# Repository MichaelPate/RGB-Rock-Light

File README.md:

# RGB Rock Light
 RGB LED decoration for a big crystal. This code is designed for an ATTiny85. Its meant to be powered over USB and just sits around as a decoration.
 This is currently v2 of the design. It uses the built in EEPROM library, the Adafruit NeoPixel library, and the ATTiny board manager URL from:
 https://raw.githubusercontent.com/damellis/attiny/ide-1.6.x-boards-manager/package_damellis_attiny_index.json

To program the board more easily, I designed a programmer shield for an Arduino Uno that lets me use a programming cable on JST PH headers.
See the link below to that repo. https://github.com/MichaelPate/Arduino-ISP-PROgrammer-Shield/tree/main

I will eventually get around to designing an enclosure for this. When that happens, ill put it on thingiverse and add the link here!
https://www.thingiverse.com/thing:7125638

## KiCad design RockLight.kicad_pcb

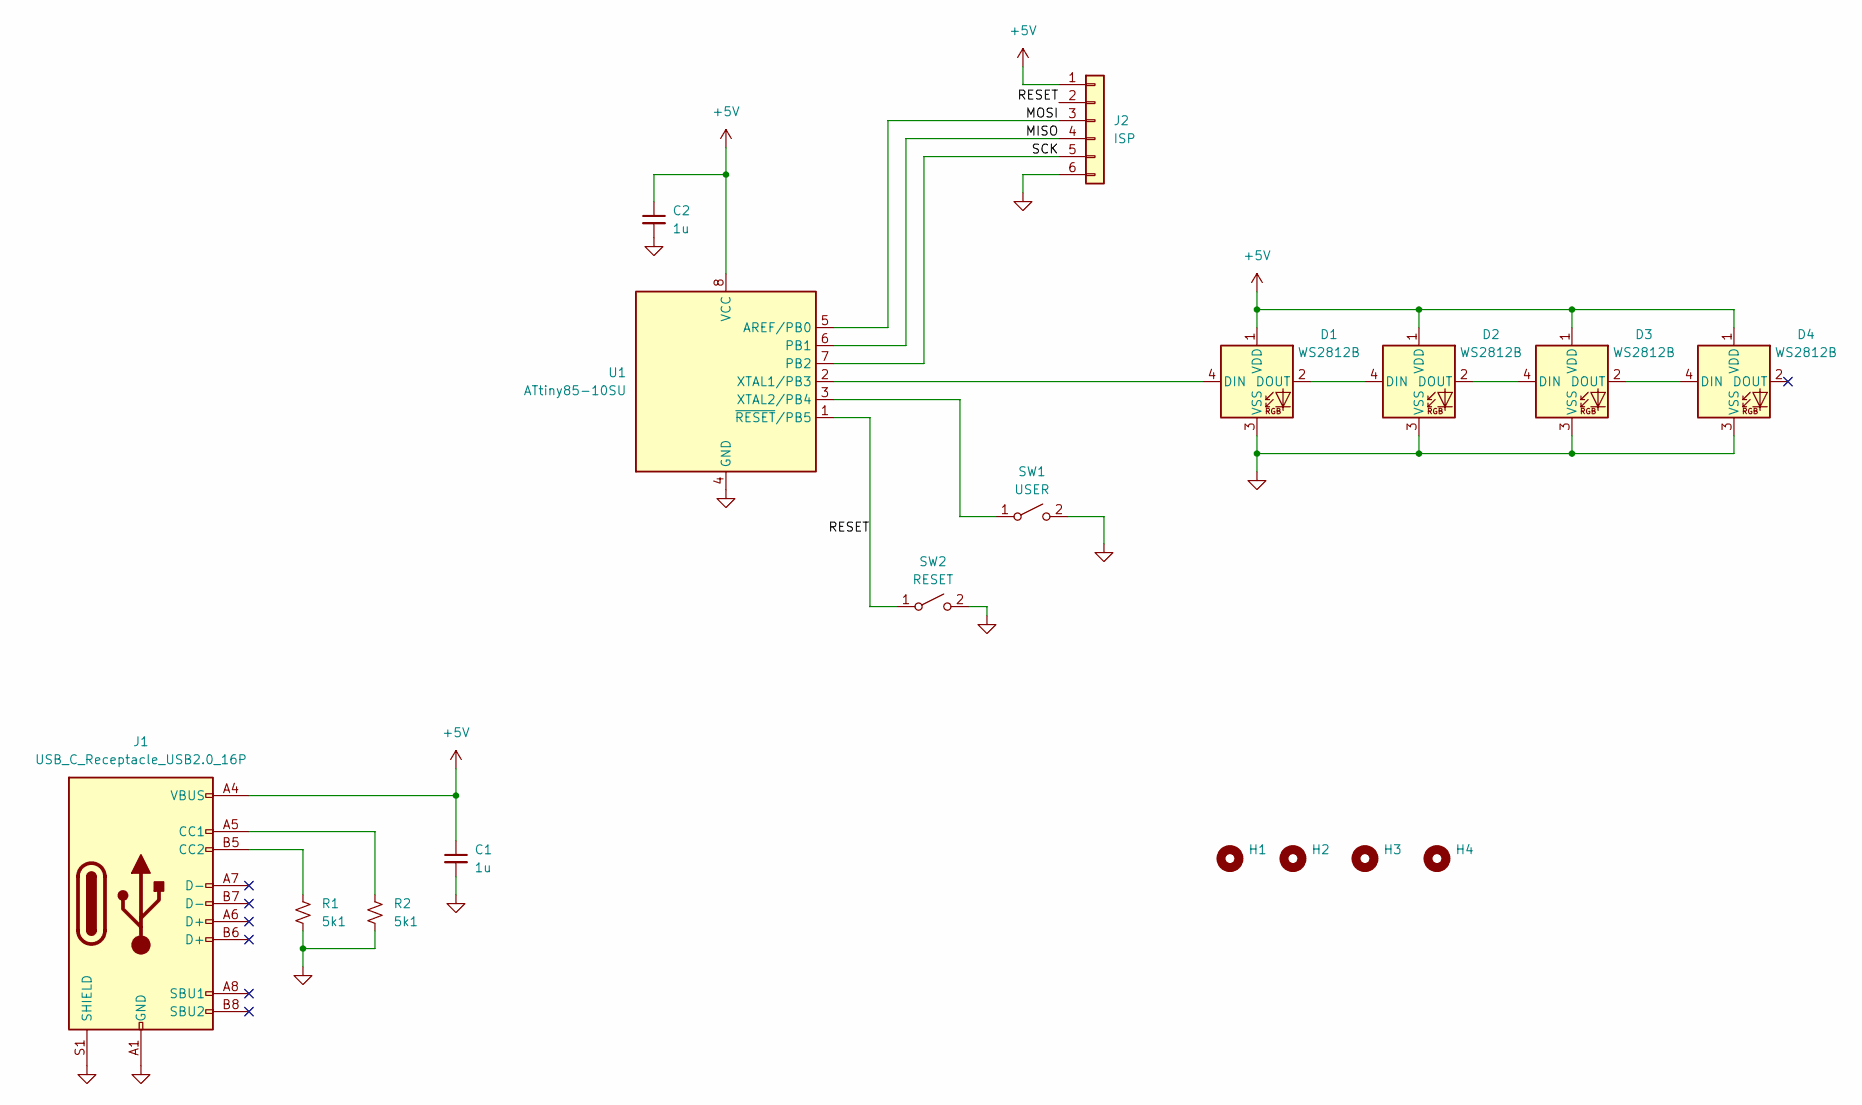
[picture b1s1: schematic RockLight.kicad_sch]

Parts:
C1, C2: 1u; C_0603_1608Metric
D1, D2, D3, D4: WS2812B; LED_WS2812B_PLCC4_5.0x5.0mm_P3.2mm
H1, H2, H3, H4: MountingHole; MountingHole_2.2mm_M2
J1: USB_C_Receptacle_USB2.0_16P; USB_C_Receptacle_G-Switch_GT-USB-7010ASV
J2: ISP; PinHeader_1x06_P2.54mm_Vertical
R1, R2: 5k1; R_0402_1005Metric
SW1: USER; SW_SPST_PTS647_Sx38
SW2: RESET; SW_SPST_PTS647_Sx38
U1: ATtiny85-10SU; SOIC-8_5.3x5.3mm_P1.27mm

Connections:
+5V: C1.1, C2.1, D1.1 (VDD), D2.1 (VDD), D3.1 (VDD), D4.1 (VDD), J1.A4 (VBUS), J1.A9 (VBUS), J1.B4 (VBUS), J1.B9 (VBUS), J2.1, U1.8 (VCC)
/MISO: J2.4, U1.6 (PB1)
/MOSI: J2.3, U1.5 (AREF/PB0)
/RESET: J2.2, SW2.1 (A), U1.1 (~RESET/PB5)
/SCK: J2.5, U1.7 (PB2)
GND: C1.2, C2.2, D1.3 (VSS), D2.3 (VSS), D3.3 (VSS), D4.3 (VSS), J1.A1 (GND), J1.A12 (GND), J1.B1 (GND), J1.B12 (GND), J1.S1 (SHIELD), J2.6, R1.1, R2.1, SW1.2 (B), SW2.2 (B), U1.4 (GND)
unnamed: D1.4 (DIN), U1.2 (XTAL1/PB3)
unnamed: D1.2 (DOUT), D2.4 (DIN)
unnamed: D2.2 (DOUT), D3.4 (DIN)
unnamed: D3.2 (DOUT), D4.4 (DIN)
unnamed: J1.A5 (CC1), R2.2
unnamed: J1.B5 (CC2), R1.2
unnamed: SW1.1 (A), U1.3 (XTAL2/PB4)

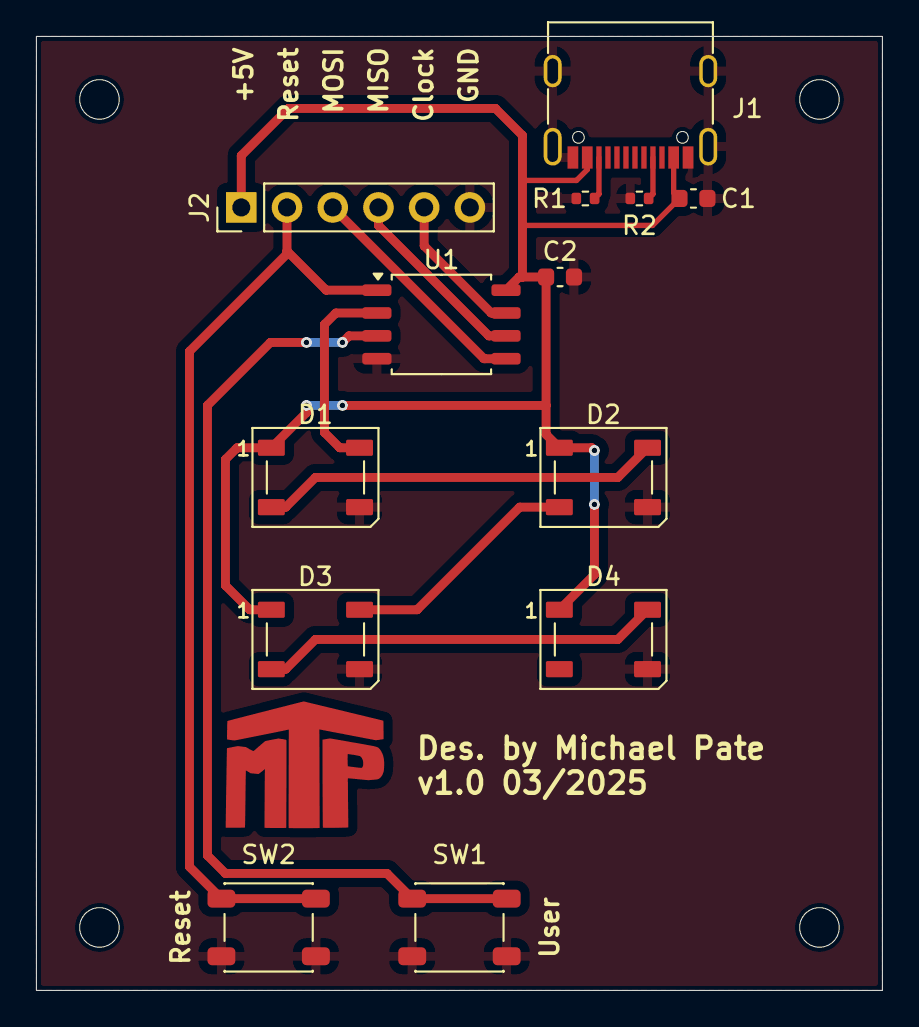
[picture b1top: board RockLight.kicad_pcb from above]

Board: 2 copper layers, 47.0 x 53.0 mm, 17 parts (0 on the bottom side), 13 nets.

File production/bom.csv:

Designator,Footprint,Quantity,Value,LCSC Part #
"C1, C2",0603,2,1u,
"D1, D2, D3, D4",LED_WS2812B_PLCC4_5.0x5.0mm_P3.2mm,4,WS2812B,
J1,USB_C_Receptacle_G-Switch_GT-USB-7010ASV,1,USB_C_Receptacle_USB2.0_16P,
J2,PinHeader_1x06_P2.54mm_Vertical,1,ISP,
"R1, R2",0402,2,5k1,
SW1,SW_SPST_PTS647_Sx38,1,USER,
SW2,SW_SPST_PTS647_Sx38,1,RESET,
U1,SOIC-8_5.3x5.3mm_P1.27mm,1,ATtiny85-10SU,

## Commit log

2025-03-29 Make circuit and PCB
2025-03-30 board files produced, PCB ordered
2025-03-30 generate 3d model
2025-08-22 Add project files
2025-08-22 move files around to be neater
2025-08-22 change source code
2025-08-22 Add 3D file for v2 PCB
2025-08-23 add more design files
2025-08-23 clean up structure
